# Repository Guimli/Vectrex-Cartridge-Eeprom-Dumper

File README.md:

# Vectrex Cartridge Eeprom Dumper
 Vectrex Cartridge Eeprom & Dumper-Programmer

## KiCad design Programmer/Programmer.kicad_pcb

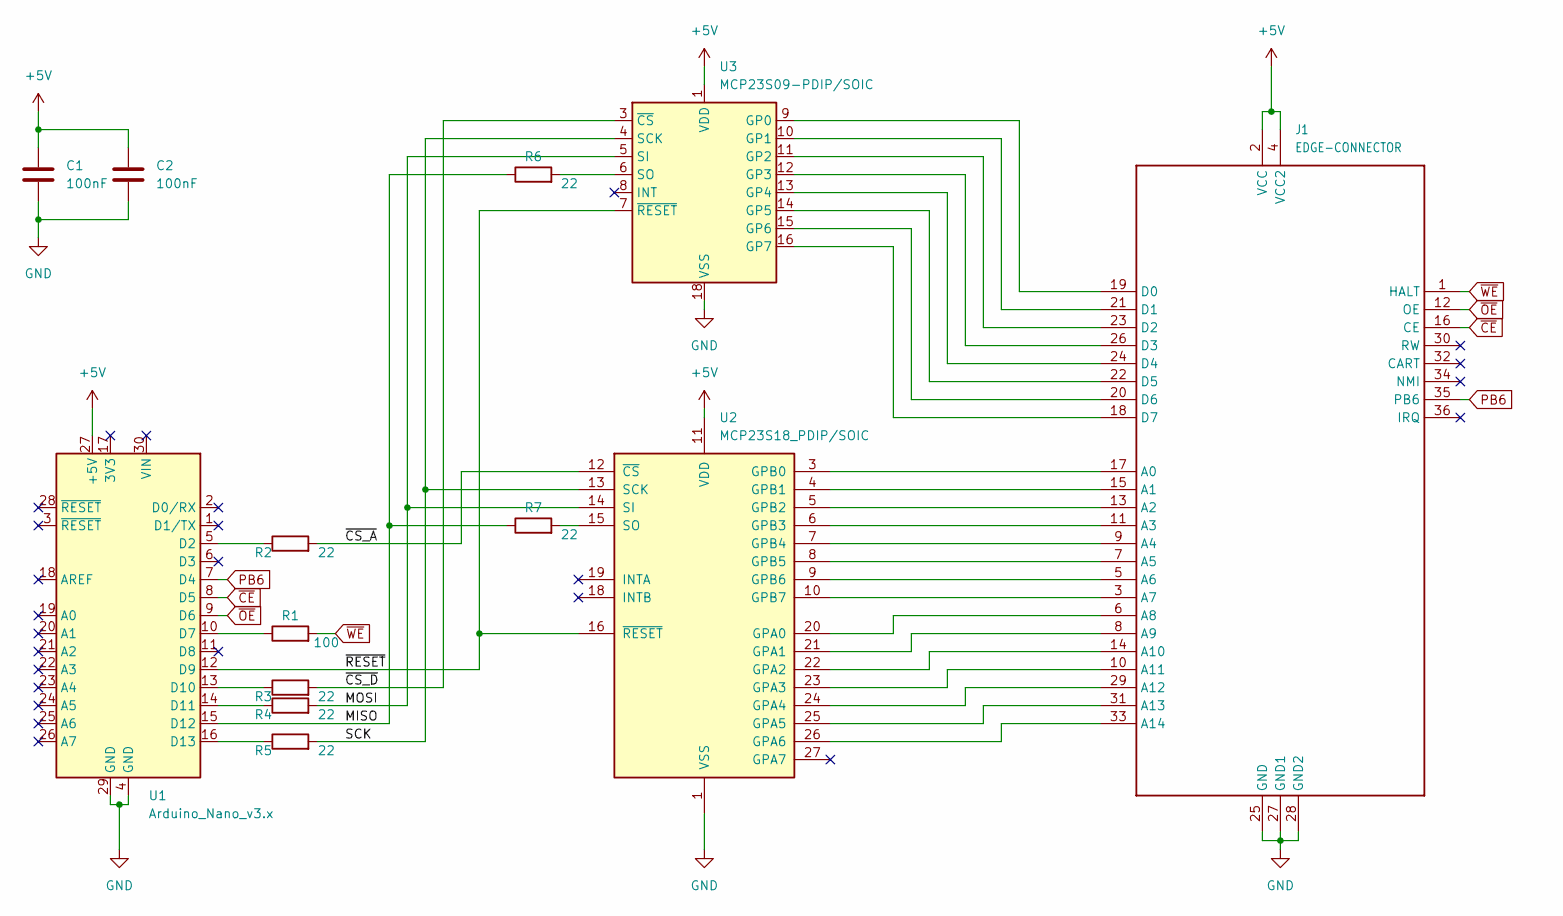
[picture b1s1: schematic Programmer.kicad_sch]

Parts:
C1, C2: 100nF; C_0805_2012Metric
J1: EDGE-CONNECTOR; CartridgeHeader_2x18_P2.54mm_Vertical
R1: 100; R_0805_2012Metric
R2, R3, R4, R5, R6, R7: 22; R_0805_2012Metric
U1: Arduino_Nano_v3.x; Arduino_Nano
U2: MCP23S18_PDIP/SOIC; SOIC-28W_7.5x17.9mm_P1.27mm
U3: MCP23S09-PDIP/SOIC; SOIC-18W_7.5x11.6mm_P1.27mm

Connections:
+5V: C1.1, C2.1, J1.2 (VCC), J1.4 (VCC2), U1.27 (+5V), U2.11 (VDD), U3.1 (VDD)
/MISO: R6.1, R7.1, U1.15 (D12)
/MOSI: R4.2, U2.14 (SI), U3.5 (SI)
/SCK: R5.2, U2.13 (SCK), U3.4 (SCK)
/~CS_A: R2.2, U2.12 (~CS)
/~CS_D: R3.2, U3.3 (~CS)
/~RESET: U1.12 (D9), U2.16 (~RESET), U3.7 (~RESET)
GND: C1.2, C2.2, J1.25 (GND), J1.27 (GND1), J1.28 (GND2), U1.4 (GND), U1.29 (GND), U2.1 (VSS), U3.18 (VSS)
unnamed: J1.3 (A7), U2.10 (GPB7)
unnamed: J1.5 (A6), U2.9 (GPB6)
unnamed: J1.6 (A8), U2.20 (GPA0)
unnamed: J1.7 (A5), U2.8 (GPB5)
unnamed: J1.8 (A9), U2.21 (GPA1)
unnamed: J1.9 (A4), U2.7 (GPB4)
unnamed: J1.10 (A11), U2.23 (GPA3)
unnamed: J1.11 (A3), U2.6 (GPB3)
unnamed: J1.13 (A2), U2.5 (GPB2)
unnamed: J1.14 (A10), U2.22 (GPA2)
unnamed: J1.15 (A1), U2.4 (GPB1)
unnamed: J1.17 (A0), U2.3 (GPB0)
unnamed: J1.18 (D7), U3.16 (GP7)
unnamed: J1.19 (D0), U3.9 (GP0)
unnamed: J1.20 (D6), U3.15 (GP6)
unnamed: J1.21 (D1), U3.10 (GP1)
unnamed: J1.22 (D5), U3.14 (GP5)
unnamed: J1.23 (D2), U3.11 (GP2)
unnamed: J1.24 (D4), U3.13 (GP4)
unnamed: J1.26 (D3), U3.12 (GP3)
unnamed: J1.29 (A12), U2.24 (GPA4)
unnamed: J1.31 (A13), U2.25 (GPA5)
unnamed: J1.33 (A14), U2.26 (GPA6)
unnamed: R1.1, U1.10 (D7)
unnamed: R2.1, U1.5 (D2)
unnamed: R3.1, U1.13 (D10)
unnamed: R4.1, U1.14 (D11)
unnamed: R5.1, U1.16 (D13)
unnamed: R6.2, U3.6 (SO)
unnamed: R7.2, U2.15 (SO)
PB6: J1.35 (PB6), U1.7 (D4)
~CE: J1.16 (CE), U1.8 (D5)
~OE: J1.12 (OE), U1.9 (D6)
~WE: J1.1 (HALT), R1.2

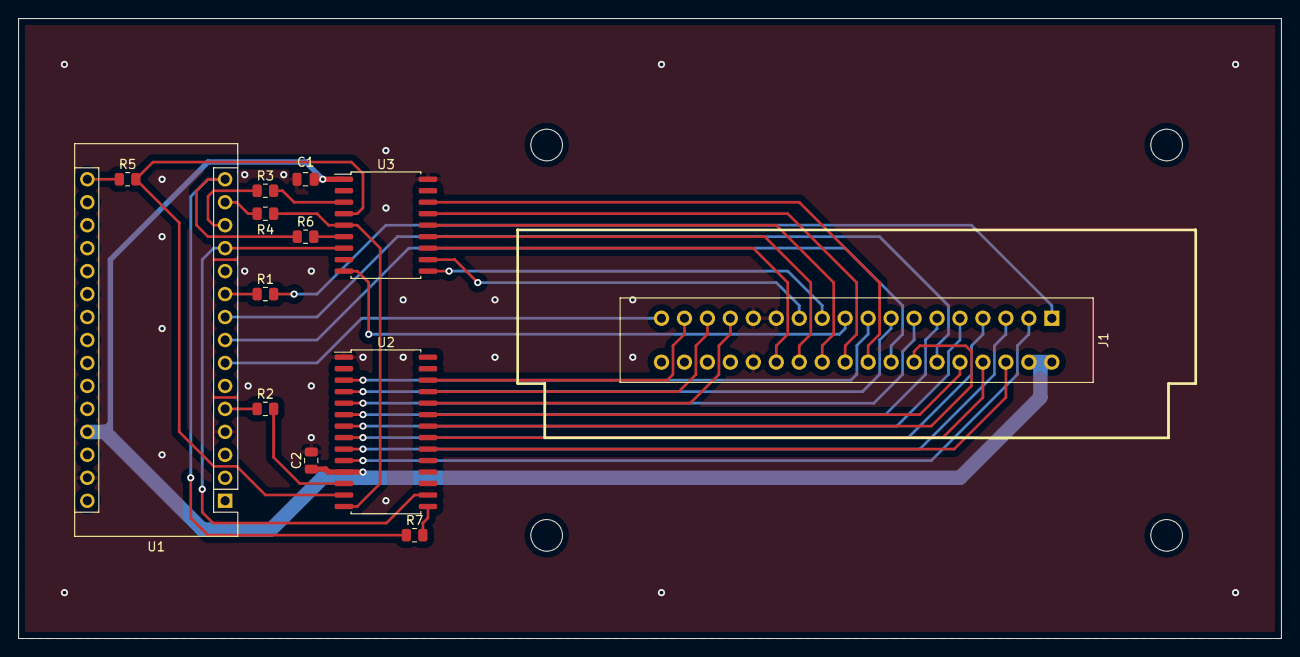
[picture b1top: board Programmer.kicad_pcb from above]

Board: 2 copper layers, 139.7 x 68.6 mm, 13 parts (0 on the bottom side), 42 nets.

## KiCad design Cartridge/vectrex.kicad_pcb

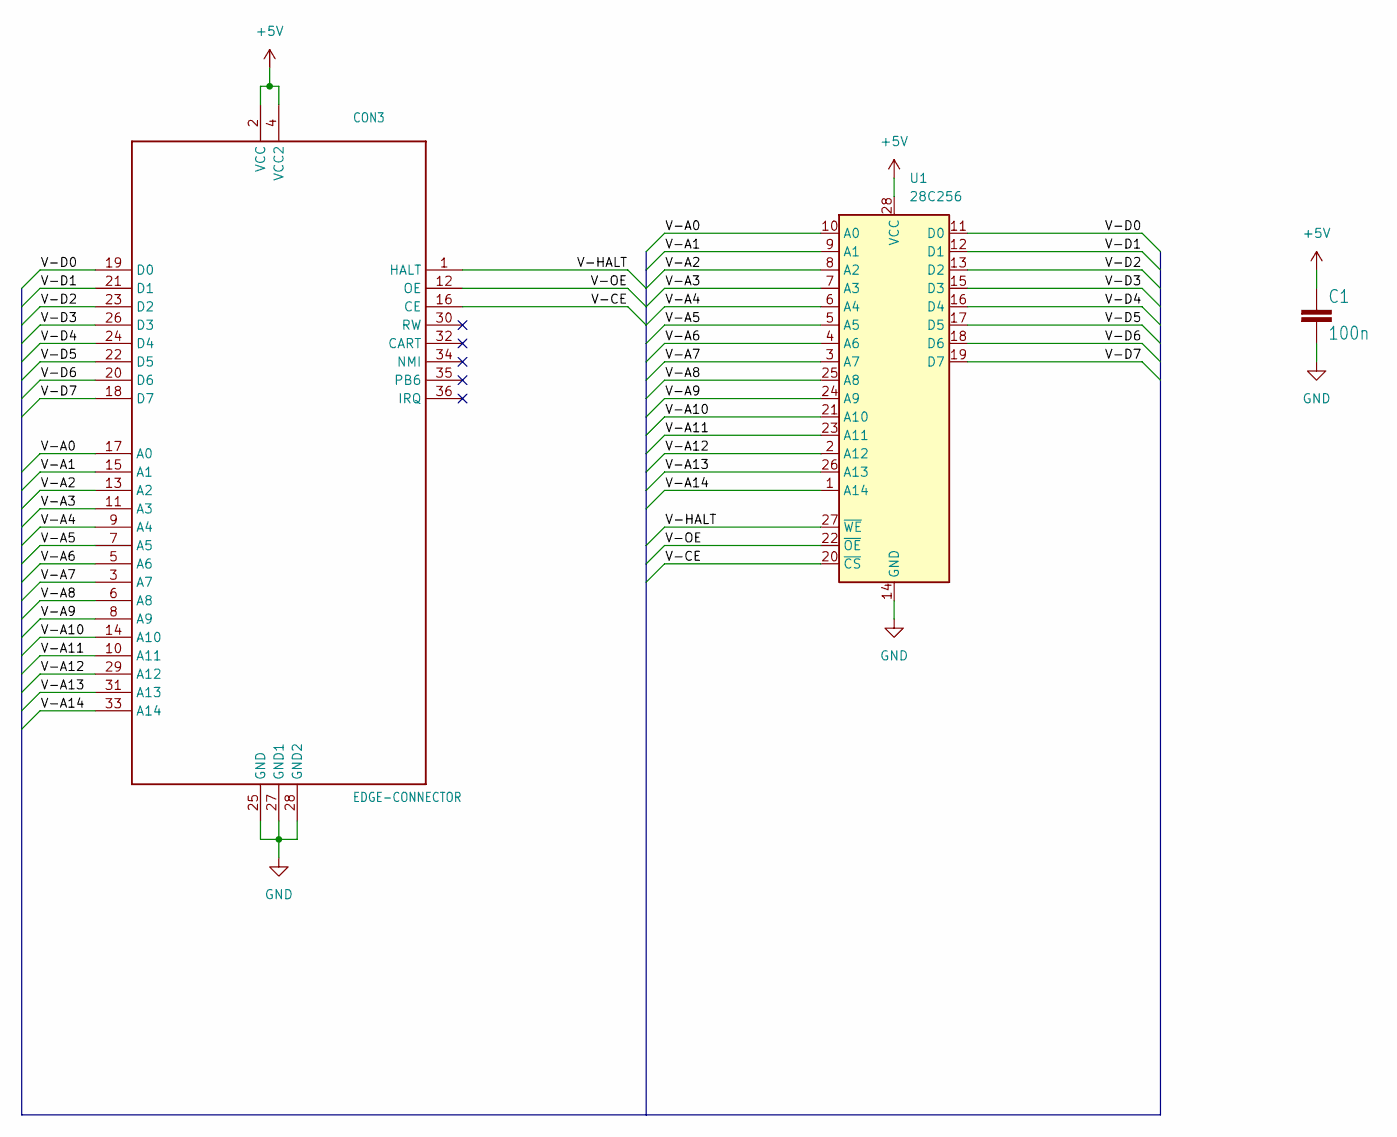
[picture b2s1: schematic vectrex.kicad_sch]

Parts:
C1: 100n; C_1206_3216Metric
CON3: EDGE-CONNECTOR
U1: 28C256; SOIC-28W_7.5x17.9mm_P1.27mm

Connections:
+5V: C1.1, CON3.2 (VCC), CON3.4 (VCC2), U1.28 (VCC)
/V-A0: CON3.17 (A0), U1.10 (A0)
/V-A1: CON3.15 (A1), U1.9 (A1)
/V-A2: CON3.13 (A2), U1.8 (A2)
/V-A3: CON3.11 (A3), U1.7 (A3)
/V-A4: CON3.9 (A4), U1.6 (A4)
/V-A5: CON3.7 (A5), U1.5 (A5)
/V-A6: CON3.5 (A6), U1.4 (A6)
/V-A7: CON3.3 (A7), U1.3 (A7)
/V-A8: CON3.6 (A8), U1.25 (A8)
/V-A9: CON3.8 (A9), U1.24 (A9)
/V-A10: CON3.14 (A10), U1.21 (A10)
/V-A11: CON3.10 (A11), U1.23 (A11)
/V-A12: CON3.29 (A12), U1.2 (A12)
/V-A13: CON3.31 (A13), U1.26 (A13)
/V-A14: CON3.33 (A14), U1.1 (A14)
/V-CE: CON3.16 (CE), U1.20 (~CS)
/V-D0: CON3.19 (D0), U1.11 (D0)
/V-D1: CON3.21 (D1), U1.12 (D1)
/V-D2: CON3.23 (D2), U1.13 (D2)
/V-D3: CON3.26 (D3), U1.15 (D3)
/V-D4: CON3.24 (D4), U1.16 (D4)
/V-D5: CON3.22 (D5), U1.17 (D5)
/V-D6: CON3.20 (D6), U1.18 (D6)
/V-D7: CON3.18 (D7), U1.19 (D7)
/V-HALT: CON3.1 (HALT), U1.27 (~WE)
/V-OE: CON3.12 (OE), U1.22 (~OE)
GND: C1.2, CON3.25 (GND), CON3.27 (GND1), CON3.28 (GND2), U1.14 (GND)

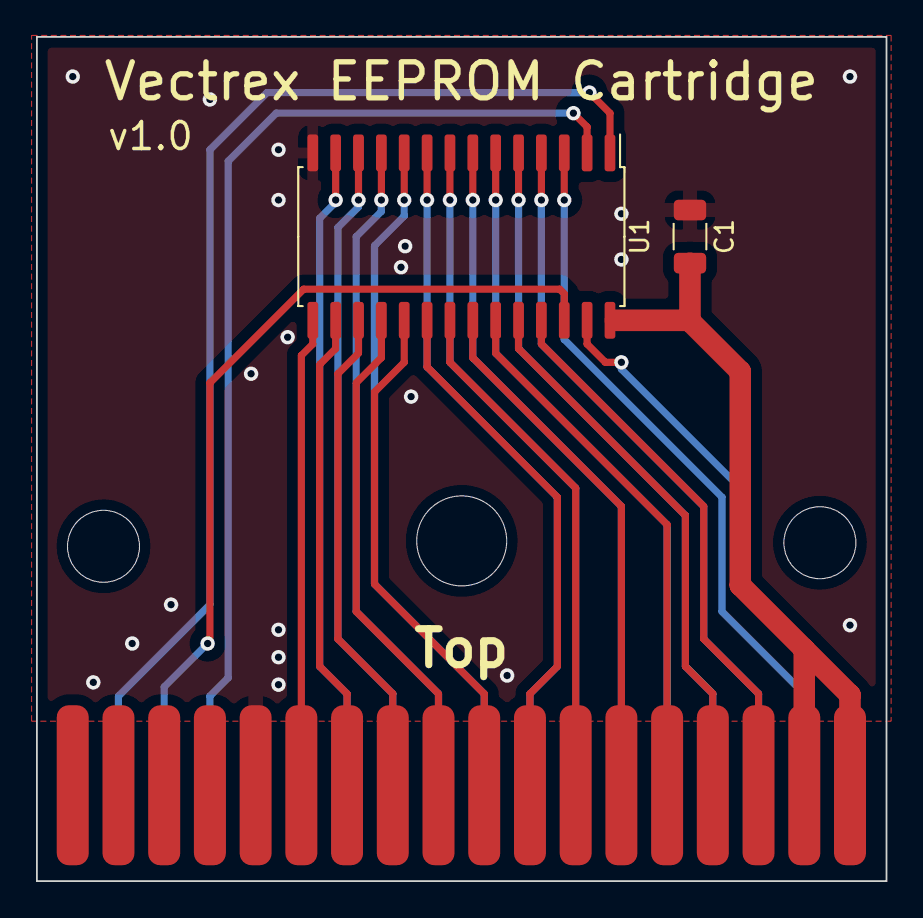
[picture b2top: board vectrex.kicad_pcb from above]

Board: 2 copper layers, 47.2 x 46.9 mm, 6 parts (0 on the bottom side), 28 nets.

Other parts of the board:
@HOLE0, @HOLE1, @HOLE2: (no value)

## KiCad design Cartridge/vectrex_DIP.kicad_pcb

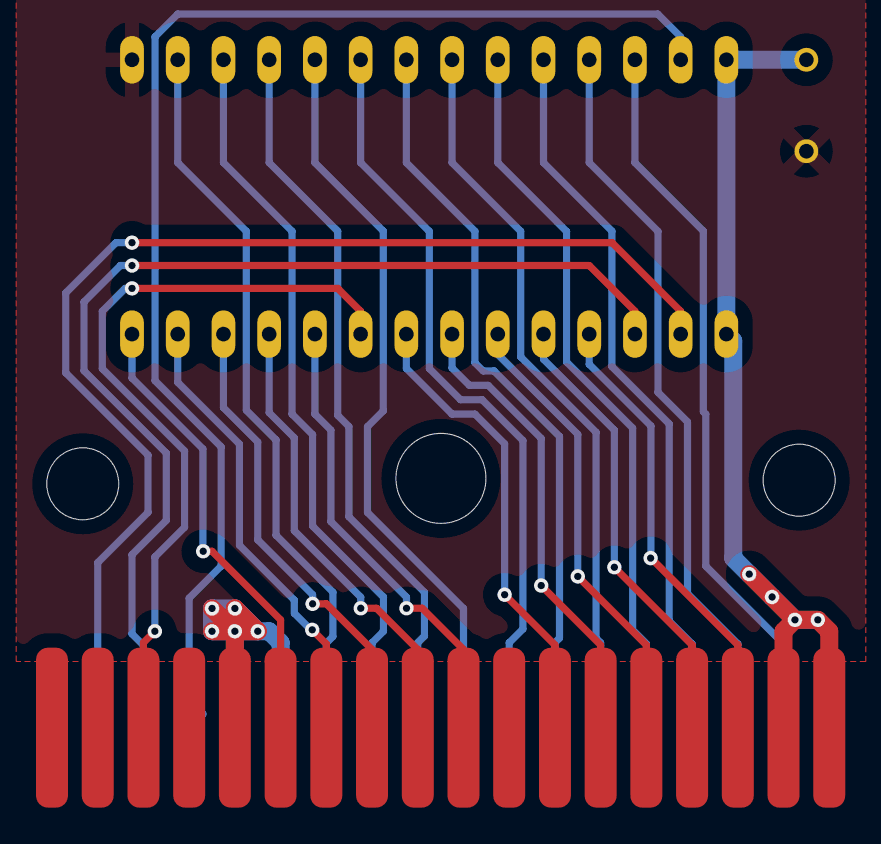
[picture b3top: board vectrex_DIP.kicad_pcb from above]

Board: 2 copper layers, 6 parts (0 on the bottom side), 27 nets.

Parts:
@HOLE0, @HOLE1, @HOLE2: (no value)
C1: 100 n; C050-045X075
CON3: EDGE-CONNECTOR
IC1: DIL28-6

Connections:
+5V: C1.1, CON3.2, CON3.4, IC1.1, IC1.28
GND: C1.2, CON3.25, CON3.27, CON3.28, IC1.14
V-A0: CON3.17, IC1.10
V-A1: CON3.15, IC1.9
V-A2: CON3.13, IC1.8
V-A3: CON3.11, IC1.7
V-A4: CON3.9, IC1.6
V-A5: CON3.7, IC1.5
V-A6: CON3.5, IC1.4
V-A7: CON3.3, IC1.3
V-A8: CON3.6, IC1.25
V-A9: CON3.8, IC1.24
V-A10: CON3.14, IC1.21
V-A11: CON3.10, IC1.23
V-A12: CON3.29, IC1.2
V-A13: CON3.31, IC1.26
V-A14: CON3.33, IC1.27
V-CART: CON3.32, IC1.20
V-D0: CON3.19, IC1.11
V-D1: CON3.21, IC1.12
V-D2: CON3.23, IC1.13
V-D3: CON3.26, IC1.15
V-D4: CON3.24, IC1.16
V-D5: CON3.22, IC1.17
V-D6: CON3.20, IC1.18
V-D7: CON3.18, IC1.19
V-OE: CON3.12, IC1.22
